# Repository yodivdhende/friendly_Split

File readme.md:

# User friendly split keyboard

# Ideas

## switch from ZMK to KMK

## RGB support

## removing the nice!nano

## other layouts

# Fixes

## pcb

- reverse mount powerplug + to -
- move power plug out of stabelizers
- connect bat streat to nice nano
- revert one switch
- move nice nano socket to center of switches

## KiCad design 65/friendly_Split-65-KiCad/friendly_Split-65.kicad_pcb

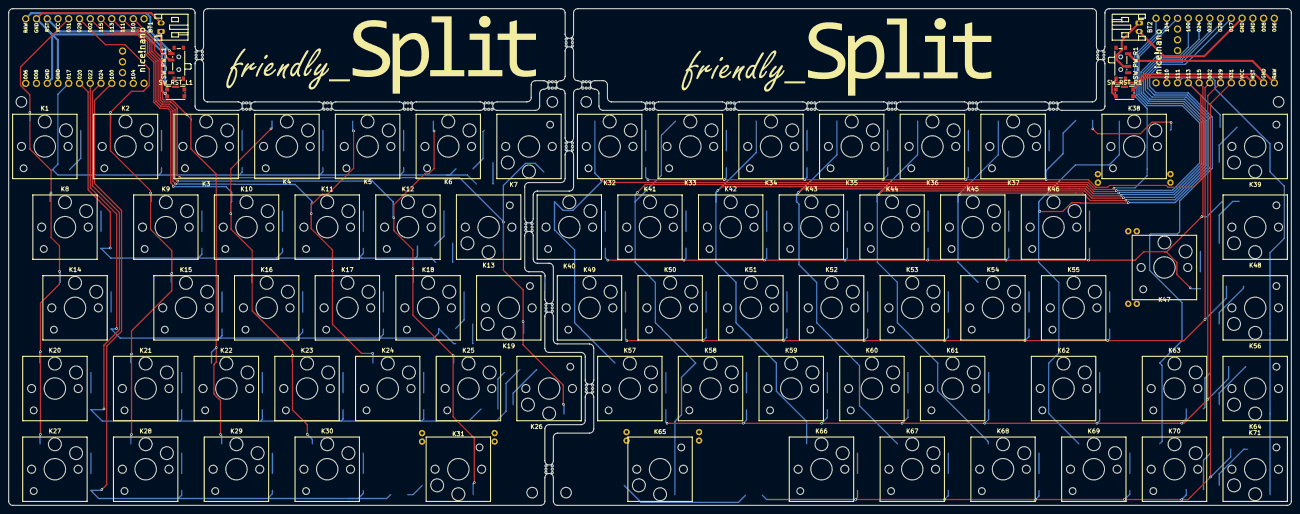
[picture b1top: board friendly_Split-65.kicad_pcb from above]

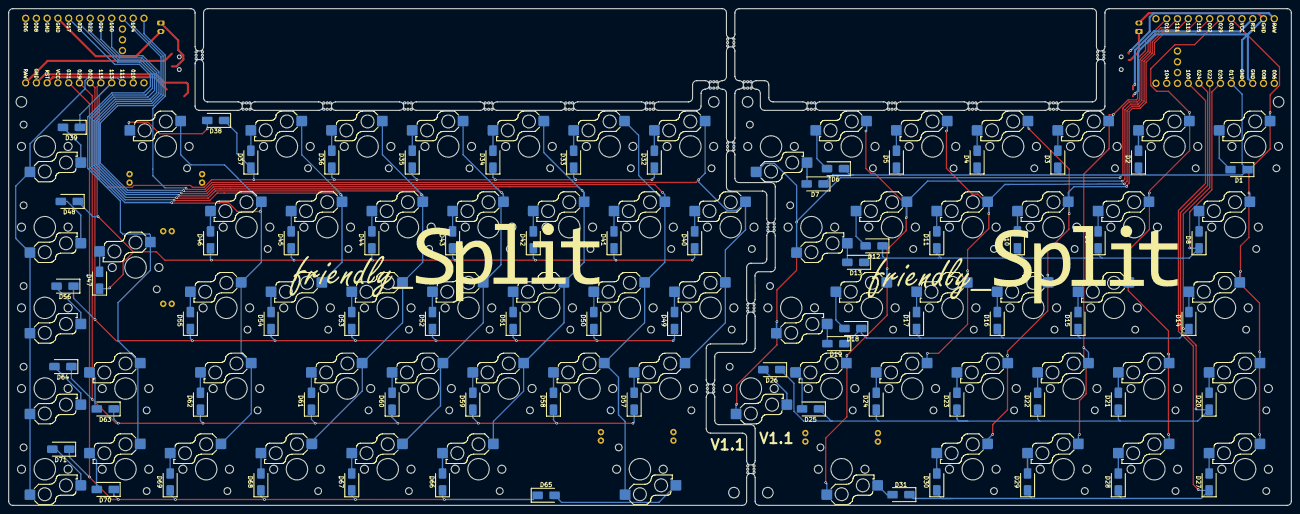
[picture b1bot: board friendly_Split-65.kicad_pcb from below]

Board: 2 copper layers, 302.8 x 117.2 mm, 174 parts (71 on the bottom side), 104 nets.

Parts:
BT1, BT2: Battery_Cell; JST_PH_S2B-PH-K_1x02_P2.00mm_Horizontal
D1, D2, D3, D4, D5, D6, D7, D8, D9, D10, D11, D12, D13, D14, D15, D16, D17, D18, D19, D20, D21, D22, D23, D24, D25, D26, D27, D28, D29, D30, D31, D32, D33, D34, D35, D36, D37, D38, D39, D40, D41, D42, D43, D44, D45, D46, D47, D48, D49, D50, D51, D52, D53, D54, D55, D56, D57, D58, D59, D60, D61, D62, D63, D64, D65, D66, D67, D68, D69, D70, D71: D; D_SMA
K1, K2, K3, K4, K5, K6, K7, K9, K10, K11, K12, K13, K15, K16, K17, K18, K19, K21, K22, K23, K24, K25, K26, K28, K30, K32, K33, K34, K35, K36, K37, K39, K40, K41, K42, K43, K44, K45, K46, K48, K49, K50, K51, K52, K53, K54, K55, K56, K57, K58, K59, K60, K61, K63, K64, K67, K69, K70, K71: SW_Hotswap_Kailh_Choc_V1V2_1.00u
K8: SW_Hotswap_Kailh_Choc_V1V2_1.50u
K14, K62: SW_Hotswap_Kailh_Choc_V1V2_1.75u
K20, K27, K29, K66, K68: SW_Hotswap_Kailh_Choc_V1V2_1.25u
K31: SW_Hotswap_Kailh_Choc_V1V2_2.25u
K38: SW_Hotswap_Kailh_Choc_V1V2_2.00u
K47: SW_Hotswap_Kailh_Choc_V1V2_ISOEnter
K65: SW_Hotswap_Kailh_Choc_V1V2_2.75u
REFe: Lowprofile_Stabilizer_2.00u
REFe#2, REFe#3, REFe#4: Lowprofile_Stabilizer_2.00u
SW_PW_L1: SW_SPDT; SW_SPDT_PCM12
SW_PW_R1: SW_SPDT; SW_SPDT_PCM12
SW_RST_L1: SW_Push; SW_Push_1P1T-SH_NO_CK_KMR2xxG
SW_RST_R1: SW_Push; SW_Push_1P1T-SH_NO_CK_KMR2xxG
U1_L1, U2_R1: nice_nano
mouse-bite-2mm-slot, mouse-bite-2mm-slot#2, mouse-bite-2mm-slot#3, mouse-bite-2mm-slot#4, mouse-bite-2mm-slot#5, mouse-bite-2mm-slot#6, mouse-bite-2mm-slot#7, mouse-bite-2mm-slot#8, mouse-bite-2mm-slot#9, mouse-bite-2mm-slot#10, mouse-bite-2mm-slot#11, mouse-bite-2mm-slot#12, mouse-bite-2mm-slot#13, mouse-bite-2mm-slot#14, mouse-bite-2mm-slot#15, mouse-bite-2mm-slot#16, mouse-bite-2mm-slot#17, mouse-bite-2mm-slot#18, mouse-bite-2mm-slot#19, mouse-bite-2mm-slot#20: VAL**; mouse-bite-2mm-slot

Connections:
Col0: K1.1 (A), K8.1 (A), K14.1 (A), K20.1 (A), K27.1 (A), U1_L1.20 (AIN7/P0.31)
Col1: K2.1 (A), K9.1 (A), K15.1 (A), K21.1 (A), K28.1 (A), U1_L1.19 (AIN5/P0.29)
Col2: K3.1 (A), K22.1 (A), K29.1 (A), U1_L1.14 (NFC2/P0.10)
Col3: K4.1 (A), K10.1 (A), K16.1 (A), K23.1 (A), K30.1 (A), U1_L1.18 (AIN0/P0.02)
Col4: K5.1 (A), K11.1 (A), K17.1 (A), K24.1 (A), U1_L1.17 (P1.15)
Col5: K6.1 (A), K12.1 (A), K18.1 (A), K25.1 (A), K31.1 (A), U1_L1.16 (P1.13)
Col6: K7.1 (A), K13.1 (A), K19.1 (A), K26.1 (A), U1_L1.15 (P1.11)
Col7: K32.1 (A), K40.1 (A), K49.1 (A), K57.1 (A), U2_R1.12 (P1.06)
Col8: K33.1 (A), K41.1 (A), K50.1 (A), K58.1 (A), K65.1 (A), U2_R1.11 (P1.04)
Col9: K34.1 (A), K42.1 (A), K51.1 (A), K59.1 (A), K66.1 (A), U2_R1.10 (P0.11)
Col10: K35.1 (A), K43.1 (A), K52.1 (A), K60.1 (A), K67.1 (A), U2_R1.9 (P1.00)
Col11: K36.1 (A), K44.1 (A), K53.1 (A), K61.1 (A), K68.1 (A), U2_R1.8 (P0.24)
Col12: K37.1 (A), K45.1 (A), K54.1 (A), U2_R1.7 (P0.22)
Col13: K38.1 (A), K46.1 (A), K55.1 (A), K62.1 (A), K69.1 (A), U2_R1.6 (P0.20)
Col14: K47.1 (A), K63.1 (A), K70.1 (A), U2_R1.5 (P0.17)
Col15: K39.1 (A), K48.1 (A), K56.1 (A), K64.1 (A), K71.1 (A), U2_R1.15 (P1.11)
GND: BT1.2 (-), BT2.2 (-), SW_RST_L1.2, SW_RST_R1.2, U1_L1.3 (GND), U1_L1.4 (GND), U1_L1.23 (GND), U2_R1.3 (GND), U2_R1.4 (GND), U2_R1.23 (GND)
unnamed: BT1.1 (+), SW_PW_L1.2 (B)
unnamed: BT2.1 (+), SW_PW_R1.2 (B)
unnamed: D1.2 (A), K1.2 (B)
unnamed: D2.2 (A), K2.2 (B)
unnamed: D3.2 (A), K3.2 (B)
unnamed: D4.2 (A), K4.2 (B)
unnamed: D5.2 (A), K5.2 (B)
unnamed: D6.2 (A), K6.2 (B)
unnamed: D7.2 (A), K7.2 (B)
unnamed: D8.2 (A), K8.2 (B)
unnamed: D9.2 (A), K9.2 (B)
unnamed: D10.2 (A), K10.2 (B)
unnamed: D11.2 (A), K11.2 (B)
unnamed: D12.2 (A), K12.2 (B)
unnamed: D13.2 (A), K13.2 (B)
unnamed: D14.2 (A), K14.2 (B)
unnamed: D15.2 (A), K15.2 (B)
unnamed: D16.2 (A), K16.2 (B)
unnamed: D17.2 (A), K17.2 (B)
unnamed: D18.2 (A), K18.2 (B)
unnamed: D19.2 (A), K19.2 (B)
unnamed: D20.2 (A), K20.2 (B)
unnamed: D21.2 (A), K21.2 (B)
unnamed: D22.2 (A), K22.2 (B)
unnamed: D23.2 (A), K23.2 (B)
unnamed: D24.2 (A), K24.2 (B)
unnamed: D25.2 (A), K25.2 (B)
unnamed: D26.2 (A), K26.2 (B)
unnamed: D27.2 (A), K27.2 (B)
unnamed: D28.2 (A), K28.2 (B)
unnamed: D29.2 (A), K29.2 (B)
unnamed: D30.2 (A), K30.2 (B)
unnamed: D31.2 (A), K31.2 (B)
unnamed: D32.2 (A), K32.2 (B)
unnamed: D33.2 (A), K33.2 (B)
unnamed: D34.2 (A), K34.2 (B)
unnamed: D35.2 (A), K35.2 (B)
unnamed: D36.2 (A), K36.2 (B)
unnamed: D37.2 (A), K37.2 (B)
unnamed: D38.2 (A), K38.2 (B)
unnamed: D39.2 (A), K39.2 (B)
unnamed: D40.2 (A), K40.2 (B)
unnamed: D41.2 (A), K41.2 (B)
unnamed: D42.2 (A), K42.2 (B)
unnamed: D43.2 (A), K43.2 (B)
unnamed: D44.2 (A), K44.2 (B)
unnamed: D45.2 (A), K45.2 (B)
unnamed: D46.2 (A), K46.2 (B)
unnamed: D47.2 (A), K47.2 (B)
unnamed: D48.2 (A), K48.2 (B)
unnamed: D49.2 (A), K49.2 (B)
unnamed: D50.2 (A), K50.2 (B)
unnamed: D51.2 (A), K51.2 (B)
unnamed: D52.2 (A), K52.2 (B)
unnamed: D53.2 (A), K53.2 (B)
unnamed: D54.2 (A), K54.2 (B)
unnamed: D55.2 (A), K55.2 (B)
unnamed: D56.2 (A), K56.2 (B)
unnamed: D57.2 (A), K57.2 (B)
unnamed: D58.2 (A), K58.2 (B)
unnamed: D59.2 (A), K59.2 (B)
unnamed: D60.2 (A), K60.2 (B)
unnamed: D61.2 (A), K61.2 (B)
unnamed: D62.2 (A), K62.2 (B)
unnamed: D63.2 (A), K63.2 (B)
unnamed: D64.2 (A), K64.2 (B)
unnamed: D65.2 (A), K65.2 (B)
unnamed: D66.2 (A), K66.2 (B)
unnamed: D67.2 (A), K67.2 (B)
unnamed: D68.2 (A), K68.2 (B)
unnamed: D69.2 (A), K69.2 (B)
unnamed: D70.2 (A), K70.2 (B)
unnamed: D71.2 (A), K71.2 (B)
unnamed: SW_PW_L1.3 (C), U1_L1.24 (BATIN/P0.04)
unnamed: SW_PW_R1.1 (A), U2_R1.24 (BATIN/P0.04)
unnamed: SW_RST_L1.1, U1_L1.22 (RST)
unnamed: SW_RST_R1.1, U2_R1.22 (RST)
Row0_L: D1.1 (K), D2.1 (K), D3.1 (K), D4.1 (K), D5.1 (K), D6.1 (K), D7.1 (K), U1_L1.5 (P0.17)
Row0_R: D32.1 (K), D33.1 (K), D34.1 (K), D35.1 (K), D36.1 (K), D37.1 (K), D38.1 (K), D39.1 (K), U2_R1.16 (P1.13)
Row1_L: D8.1 (K), D9.1 (K), D10.1 (K), D11.1 (K), D12.1 (K), D13.1 (K), U1_L1.6 (P0.20)
Row1_R: D40.1 (K), D41.1 (K), D42.1 (K), D43.1 (K), D44.1 (K), D45.1 (K), D46.1 (K), D47.1 (K), D48.1 (K), U2_R1.17 (P1.15)
Row2_L: D14.1 (K), D15.1 (K), D16.1 (K), D17.1 (K), D18.1 (K), D19.1 (K), U1_L1.7 (P0.22)
Row2_R: D49.1 (K), D50.1 (K), D51.1 (K), D52.1 (K), D53.1 (K), D54.1 (K), D55.1 (K), D56.1 (K), U2_R1.18 (AIN0/P0.02)
Row3_L: D20.1 (K), D21.1 (K), D22.1 (K), D23.1 (K), D24.1 (K), D25.1 (K), D26.1 (K), U1_L1.8 (P0.24)
Row3_R: D57.1 (K), D58.1 (K), D59.1 (K), D60.1 (K), D61.1 (K), D62.1 (K), D63.1 (K), D64.1 (K), U2_R1.19 (AIN5/P0.29)
Row4_L: D27.1 (K), D28.1 (K), D29.1 (K), D30.1 (K), D31.1 (K), U1_L1.9 (P1.00)
Row4_R: D65.1 (K), D66.1 (K), D67.1 (K), D68.1 (K), D69.1 (K), D70.1 (K), D71.1 (K), U2_R1.20 (AIN7/P0.31)

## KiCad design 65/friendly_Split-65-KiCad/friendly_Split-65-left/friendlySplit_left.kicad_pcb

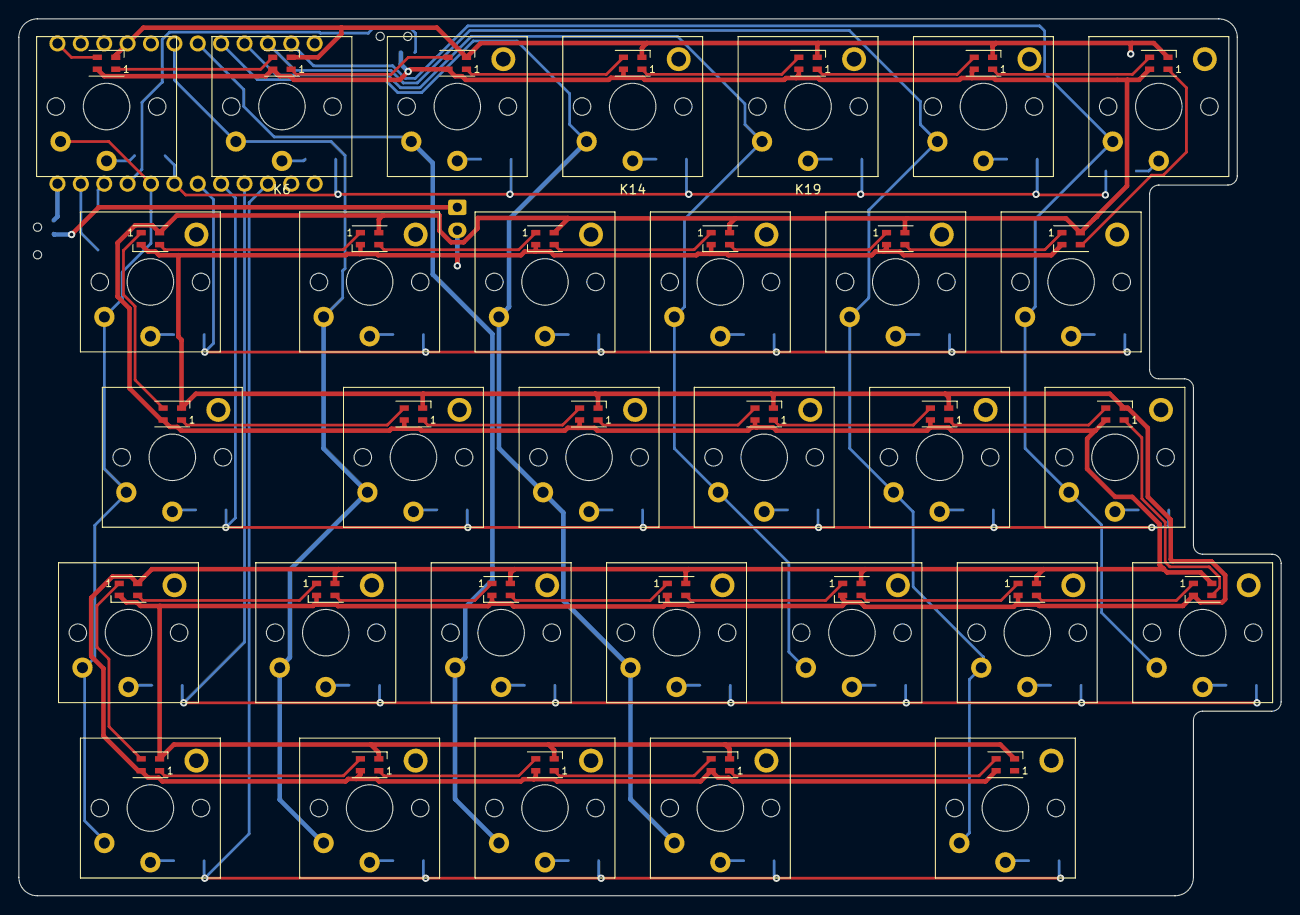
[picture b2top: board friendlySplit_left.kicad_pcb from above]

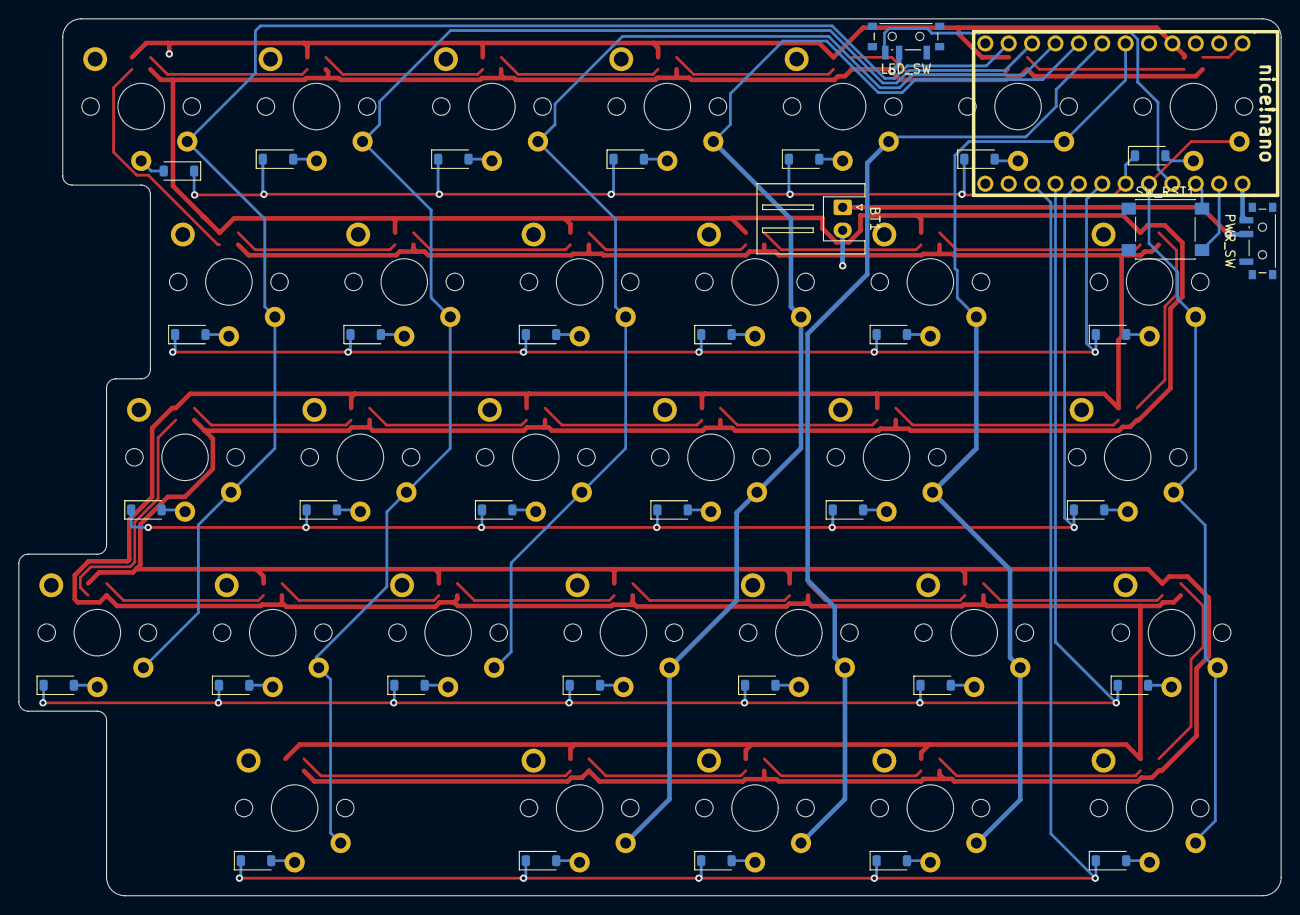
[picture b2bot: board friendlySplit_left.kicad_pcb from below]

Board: 2 copper layers, 137.1 x 95.2 mm, 98 parts (36 on the bottom side), 80 nets.

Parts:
BT1: Battery_Cell; JST_XH_S2B-XH-A_1x02_P2.50mm_Horizontal
D1, D2, D3, D4, D5, D6, D7, D8, D9, D10, D11, D12, D13, D14, D15, D16, D17, D18, D19, D20, D21, D22, D23, D24, D25, D26, D27, D28, D29, D30, D31: D; D_SOD-123
D32, D33, D34, D35, D36, D37, D38, D39, D40, D41, D42, D43, D44, D45, D46, D47, D48, D49, D50, D51, D52, D53, D54, D55, D56, D57, D58, D59, D60, D61, D62: SK6812MINI; LED_SK6805_PLCC4_2.4x2.7mm_P1.3mm
K1, K6, K7, K8, K9, K10, K11, K12, K13, K14, K15, K16, K17, K18, K19, K20, K21, K22, K24, K25, K26, K27, K28, K29, K30, K31: KEYSW; SW_Kailh_Choc_V1V2_1.00u
K2, K5: KEYSW; SW_Kailh_Choc_V1V2_1.50u
K3: KEYSW; SW_Kailh_Choc_V1V2_1.75u
K4: KEYSW; SW_Kailh_Choc_V1V2_1.25u
K23: KEYSW; SW_Kailh_Choc_V1V2_2.25u
LED_SW: SW_SPDT; SW_SPDT_PCM12
PWR_SW: SW_SPDT; SW_SPDT_PCM12
SW_RST1: SW_Push; SW_Push_1P1T_NO_6x6mm_H9.5mm
U1: nice_nano; nice_nano_mod

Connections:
+5V: BT1.2 (-), D32.2 (VSS), D33.2 (VSS), D34.2 (VSS), D35.2 (VSS), D36.2 (VSS), D37.2 (VSS), D38.2 (VSS), D39.2 (VSS), D40.2 (VSS), D41.2 (VSS), D42.2 (VSS), D43.2 (VSS), D44.2 (VSS), D45.2 (VSS), D46.2 (VSS), D47.2 (VSS), D48.2 (VSS), D49.2 (VSS), D50.2 (VSS), D51.2 (VSS), D52.2 (VSS), D53.2 (VSS), D54.2 (VSS), D55.2 (VSS), D56.2 (VSS), D57.2 (VSS), D58.2 (VSS), D59.2 (VSS), D60.2 (VSS), D61.2 (VSS), D62.2 (VSS), SW_RST1.2, U1.3 (GND), U1.4 (GND), U1.23 (GND)
Col0: K1.2, K2.2, K3.2, K4.2, K5.2, U1.20 (AIN7/P0.31)
Col1: K6.2, K7.2, K8.2, K9.2, K10.2, U1.6 (P0.20)
Col2: K11.2, K12.2, K13.2, U1.7 (P0.22)
Col3: K14.2, K15.2, K16.2, K17.2, K18.2, U1.8 (P0.24)
Col4: K19.2, K20.2, K21.2, K22.2, U1.9 (P1.00)
Col5: K23.2, K24.2, K25.2, K26.2, K27.2, U1.10 (P0.11)
Col6: K28.2, K29.2, K30.2, K31.2, U1.11 (P1.04)
unnamed: BT1.1 (+), PWR_SW.2 (B)
unnamed: D1.2 (A), K1.1
unnamed: D2.2 (A), K2.1
unnamed: D3.2 (A), K3.1
unnamed: D4.2 (A), K4.1
unnamed: D5.2 (A), K5.1
unnamed: D6.2 (A), K6.1
unnamed: D7.2 (A), K7.1
unnamed: D8.2 (A), K8.1
unnamed: D9.2 (A), K9.1
unnamed: D10.2 (A), K10.1
unnamed: D11.2 (A), K11.1
unnamed: D12.2 (A), K12.1
unnamed: D13.2 (A), K13.1
unnamed: D14.2 (A), K14.1
unnamed: D15.2 (A), K15.1
unnamed: D16.2 (A), K16.1
unnamed: D17.2 (A), K17.1
unnamed: D18.2 (A), K18.1
unnamed: D19.2 (A), K19.1
unnamed: D20.2 (A), K20.1
unnamed: D21.2 (A), K21.1
unnamed: D22.2 (A), K22.1
unnamed: D23.2 (A), K24.1
unnamed: D24.2 (A), K25.1
unnamed: D25.2 (A), K26.1
unnamed: D26.2 (A), K27.1
unnamed: D27.2 (A), K23.1
unnamed: D28.2 (A), K28.1
unnamed: D29.2 (A), K29.1
unnamed: D30.2 (A), K30.1
unnamed: D31.2 (A), K31.1
unnamed: D32.1 (DOUT), D33.3 (DIN)
unnamed: D33.1 (DOUT), D34.3 (DIN)
unnamed: D34.1 (DOUT), D35.3 (DIN)
unnamed: D35.1 (DOUT), D36.3 (DIN)
unnamed: D36.1 (DOUT), D37.3 (DIN)
unnamed: D37.1 (DOUT), D38.3 (DIN)
unnamed: D38.1 (DOUT), D44.3 (DIN)
unnamed: D39.3 (DIN), D40.1 (DOUT)
unnamed: D39.1 (DOUT), D45.3 (DIN)
unnamed: D40.3 (DIN), D41.1 (DOUT)
unnamed: D41.3 (DIN), D42.1 (DOUT)
unnamed: D42.3 (DIN), D43.1 (DOUT)
unnamed: D43.3 (DIN), D44.1 (DOUT)
unnamed: D45.1 (DOUT), D46.3 (DIN)
unnamed: D46.1 (DOUT), D47.3 (DIN)
unnamed: D47.1 (DOUT), D48.3 (DIN)
unnamed: D48.1 (DOUT), D49.3 (DIN)
unnamed: D49.1 (DOUT), D50.3 (DIN)
unnamed: D50.1 (DOUT), D57.3 (DIN)
unnamed: D51.3 (DIN), D52.1 (DOUT)
unnamed: D51.1 (DOUT), D58.3 (DIN)
unnamed: D52.3 (DIN), D53.1 (DOUT)
unnamed: D53.3 (DIN), D54.1 (DOUT)
unnamed: D54.3 (DIN), D55.1 (DOUT)
unnamed: D55.3 (DIN), D56.1 (DOUT)
unnamed: D56.3 (DIN), D57.1 (DOUT)
unnamed: D58.1 (DOUT), D59.3 (DIN)
unnamed: D59.1 (DOUT), D60.3 (DIN)
unnamed: D60.1 (DOUT), D61.3 (DIN)
unnamed: D61.1 (DOUT), D62.3 (DIN)
unnamed: PWR_SW.3 (C), U1.24 (BATIN/P0.04)
unnamed: LED_SW.3 (C), U1.21 (VCC)
unnamed: SW_RST1.1, U1.22 (RST)
Row0: D1.1 (K), D6.1 (K), D11.1 (K), D14.1 (K), D19.1 (K), D23.1 (K), D28.1 (K), U1.19 (AIN5/P0.29)
Row1: D2.1 (K), D7.1 (K), D15.1 (K), D20.1 (K), D24.1 (K), D29.1 (K), U1.18 (AIN0/P0.02)
Row2: D3.1 (K), D8.1 (K), D16.1 (K), D21.1 (K), D25.1 (K), D30.1 (K), U1.17 (P1.15)
Row3: D4.1 (K), D9.1 (K), D12.1 (K), D17.1 (K), D22.1 (K), D26.1 (K), D31.1 (K), U1.16 (P1.13)
Row4: D5.1 (K), D10.1 (K), D13.1 (K), D18.1 (K), D27.1 (K), U1.15 (P1.11)
TXD: D32.3 (DIN), U1.1 (TX0/P0.06)
VCC: D32.4 (VDD), D33.4 (VDD), D34.4 (VDD), D35.4 (VDD), D36.4 (VDD), D37.4 (VDD), D38.4 (VDD), D39.4 (VDD), D40.4 (VDD), D41.4 (VDD), D42.4 (VDD), D43.4 (VDD), D44.4 (VDD), D45.4 (VDD), D46.4 (VDD), D47.4 (VDD), D48.4 (VDD), D49.4 (VDD), D50.4 (VDD), D51.4 (VDD), D52.4 (VDD), D53.4 (VDD), D54.4 (VDD), D55.4 (VDD), D56.4 (VDD), D57.4 (VDD), D58.4 (VDD), D59.4 (VDD), D60.4 (VDD), D61.4 (VDD), D62.4 (VDD), LED_SW.2 (B)

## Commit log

2023-06-05 adding 65 files
2023-06-07 adding readme
2023-07-03 adding the schematics to project
2023-09-24 pcb done
2023-09-24 adding fab folder to gitignore
2023-09-24 fixing git ignore
2023-09-24 adding gerber file config
2023-10-12 removing zips
2023-10-12 updating 65 firmware to v1.1.0
2024-02-24 updadting
